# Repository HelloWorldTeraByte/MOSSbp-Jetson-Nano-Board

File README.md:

# MOSSbp-Jetson-Nano-Board
MOSSbp(Multi-material Open Source Secure Bio Printer) is an IoT connected bio printer. This is a daughter board for the jetson nano.

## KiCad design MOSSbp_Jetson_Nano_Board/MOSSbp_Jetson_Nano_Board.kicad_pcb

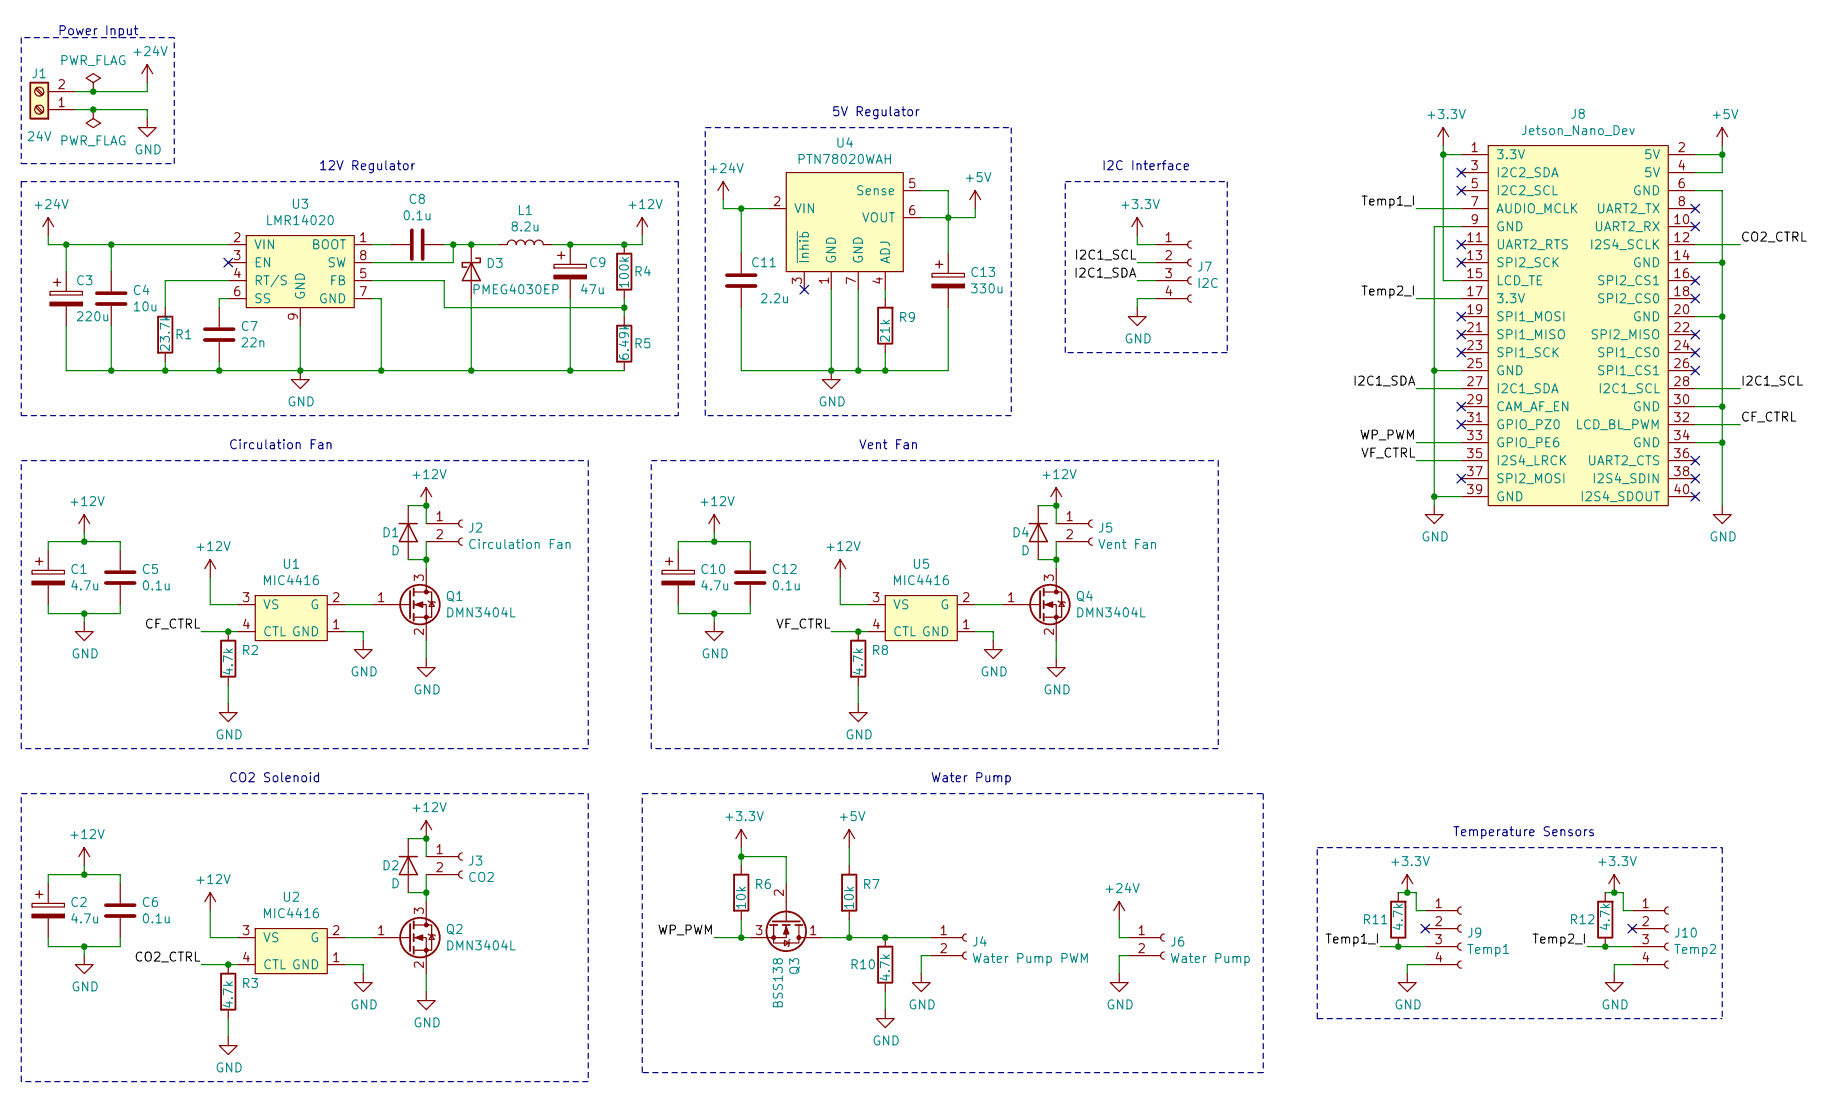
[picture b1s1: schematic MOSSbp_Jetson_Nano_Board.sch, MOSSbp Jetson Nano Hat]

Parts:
C1, C2, C10: 4.7u; C_1206_3216Metric_Pad1.42x1.75mm_HandSolder; Digi-Key_PN 478-11461-1-ND
C3: 220u; CP_Elec_8x10.5; Digi-Key_PN PCE5025CT-ND
C4: 10u; C_1206_3216Metric_Pad1.42x1.75mm_HandSolder; Digi-Key_PN 1276-6767-1-ND
C5, C6, C12: 0.1u; C_0603_1608Metric_Pad1.05x0.95mm_HandSolder; Digi-Key_PN 399-7845-1-ND
C7: 22n; C_0603_1608Metric_Pad1.05x0.95mm_HandSolder; Digi-Key_PN 399-3476-1-ND
C8: 0.1u; C_0603_1608Metric_Pad1.05x0.95mm_HandSolder; Digi-Key_PN 311-1341-1-ND
C9: 47u; C_2220_5650Metric_Pad1.97x5.40mm_HandSolder; Digi-Key_PN 445-7935-1-ND
C11: 2.2u; C_0603_1608Metric_Pad1.05x0.95mm_HandSolder; Digi-Key_PN 490-10486-1-ND
C13: 330u; CP_Elec_8x10; Digi-Key_PN PCE3888CT-ND
D1, D2, D4: D; D_SOD-123; Digi-Key_PN MBR130T1GOSDKR-ND
D3: PMEG4030EP; D_SOD-128; Digi-Key_PN 1727-5841-1-ND
J1: 24V; TerminalBlock_Phoenix_MKDS-1,5-2_1x02_P5.00mm_Horizontal; Digi-Key_PN 277-1667-ND
J2: Circulation Fan; JST_GH_BM02B-GHS-TBT_1x02-1MP_P1.25mm_Vertical; Digi-Key_PN 455-1578-1-ND
J3: CO2; JST_GH_BM02B-GHS-TBT_1x02-1MP_P1.25mm_Vertical; Digi-Key_PN 455-1578-1-ND
J4: Water Pump PWM; JST_GH_BM02B-GHS-TBT_1x02-1MP_P1.25mm_Vertical; Digi-Key_PN 455-1578-1-ND
J5: Vent Fan; JST_GH_BM02B-GHS-TBT_1x02-1MP_P1.25mm_Vertical; Digi-Key_PN 455-1578-1-ND
J6: Water Pump; JST_XH_B2B-XH-AM_1x02_P2.50mm_Vertical; Digi-Key_PN 455-2247-ND
J7: I2C; JST_GH_BM04B-GHS-TBT_1x04-1MP_P1.25mm_Vertical; Digi-Key_PN 455-1580-1-ND
J8: Jetson_Nano_Dev; PinHeader_2x20_P2.54mm_Vertical
J9: Temp1; JST_GH_BM04B-GHS-TBT_1x04-1MP_P1.25mm_Vertical; Digi-Key_PN 455-1580-1-ND
J10: Temp2; JST_GH_BM04B-GHS-TBT_1x04-1MP_P1.25mm_Vertical; Digi-Key_PN 455-1580-1-ND
L1: 8.2u; SRN8040-8R2Y; Digi-Key_PN SRN8040-8R2YCT-ND
Q1, Q2, Q4: DMN3404L; SOT-23; Digi-Key_PN DMN3404LDICT-ND
Q3: BSS138; SOT-23; Digi-Key_PN BSS138CT-ND
R1: 23.7k; R_0603_1608Metric_Pad1.05x0.95mm_HandSolder; Digi-Key_PN P23.7KHCT-ND
R2, R3, R8, R10, R11, R12: 4.7k; R_0603_1608Metric_Pad1.05x0.95mm_HandSolder; Digi-Key_PN 311-4.7KGRCT-ND
R4: 100k; R_0603_1608Metric_Pad1.05x0.95mm_HandSolder; Digi-Key_PN P100KDBCT-ND
R5: 6.49k; R_0603_1608Metric_Pad1.05x0.95mm_HandSolder; Digi-Key_PN P20065CT-ND
R6, R7: 10k; R_0603_1608Metric_Pad1.05x0.95mm_HandSolder; Digi-Key_PN 311-10.0KHRCT-ND
R9: 21k; R_0603_1608Metric_Pad1.05x0.95mm_HandSolder; Digi-Key_PN P21.0KHCT-ND
U1, U2, U5: MIC4416; SOT-143; Digi-Key_PN 576-1187-1-ND
U3: LMR14020; SOIC-8-1EP_3.9x4.9mm_P1.27mm_EP2.41x3.3mm; Digi-Key_PN 296-44320-1-ND
U4: PTN78020WAH; Digi-Key_PN 296-20515-ND

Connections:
+3V3: J7.1, J8.1 (3.3V), J8.15 (LCD_TE), J9.1, J10.1, Q3.2 (G), R6.1, R11.2, R12.2
+5V: C13.1, J8.2 (5V), J8.4 (5V), R7.1, U4.5 (Sense), U4.6 (VOUT)
+12V: C1.1, C2.1, C5.1, C6.1, C9.1, C10.1, C12.1, D1.1 (K), D2.1 (K), D4.1 (K), J2.1, J3.1, J5.1, L1.2, R4.1, U1.3 (VS), U2.3 (VS), U5.3 (VS)
+24V: C3.1, C4.1, C11.1, J1.2, J6.1, U3.2 (VIN), U4.2 (VIN)
/CF_CTRL: J8.32 (LCD_BL_PWM), R2.1, U1.4 (CTL)
/CO2_CTRL: J8.12 (I2S4_SCLK), R3.1, U2.4 (CTL)
/I2C1_SCL: J7.2, J8.28 (I2C1_SCL)
/I2C1_SDA: J7.3, J8.27 (I2C1_SDA)
/Temp1_I: J8.7 (AUDIO_MCLK), J9.3, R11.1
/Temp2_I: J8.17 (3.3V), J10.3, R12.1
/VF_CTRL: J8.35 (I2S4_LRCK), R8.1, U5.4 (CTL)
/WP_PWM: J8.33 (GPIO_PE6), Q3.3 (S), R6.2
GND: C1.2, C2.2, C3.2, C4.2, C5.2, C6.2, C7.2, C9.2, C10.2, C11.2, C12.2, C13.2, D3.2 (A), J1.1, J4.2, J6.2, J7.4, J8.6 (GND), J8.9 (GND), J8.14 (GND), J8.20 (GND), J8.25 (GND), J8.30 (GND), J8.34 (GND), J8.39 (GND), J9.4, J10.4, Q1.2 (S), Q2.2 (S), Q4.2 (S), R1.2, R2.2, R3.2, R5.2, R8.2, R9.1, R10.2, U1.1 (GND), U2.1 (GND), U3.7 (GND), U3.9 (GND), U4.1 (GND), U4.7 (GND), U5.1 (GND)
unnamed: C7.1, U3.6 (SS)
unnamed: C8.1, D3.1 (K), L1.1, U3.8 (SW)
unnamed: C8.2, U3.1 (BOOT)
unnamed: D1.2 (A), J2.2, Q1.3 (D)
unnamed: D2.2 (A), J3.2, Q2.3 (D)
unnamed: D4.2 (A), J5.2, Q4.3 (D)
unnamed: J4.1, Q3.1 (D), R7.2, R10.1
unnamed: Q1.1 (G), U1.2 (G)
unnamed: Q2.1 (G), U2.2 (G)
unnamed: Q4.1 (G), U5.2 (G)
unnamed: R1.1, U3.4 (RT/S)
unnamed: R4.2, R5.1, U3.5 (FB)
unnamed: R9.2, U4.4 (ADJ)

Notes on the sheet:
12V Regulator
Power Input
Circulation Fan
Vent Fan
CO2 Solenoid
Water Pump
5V Regulator
I2C Interface
Temperature Sensors

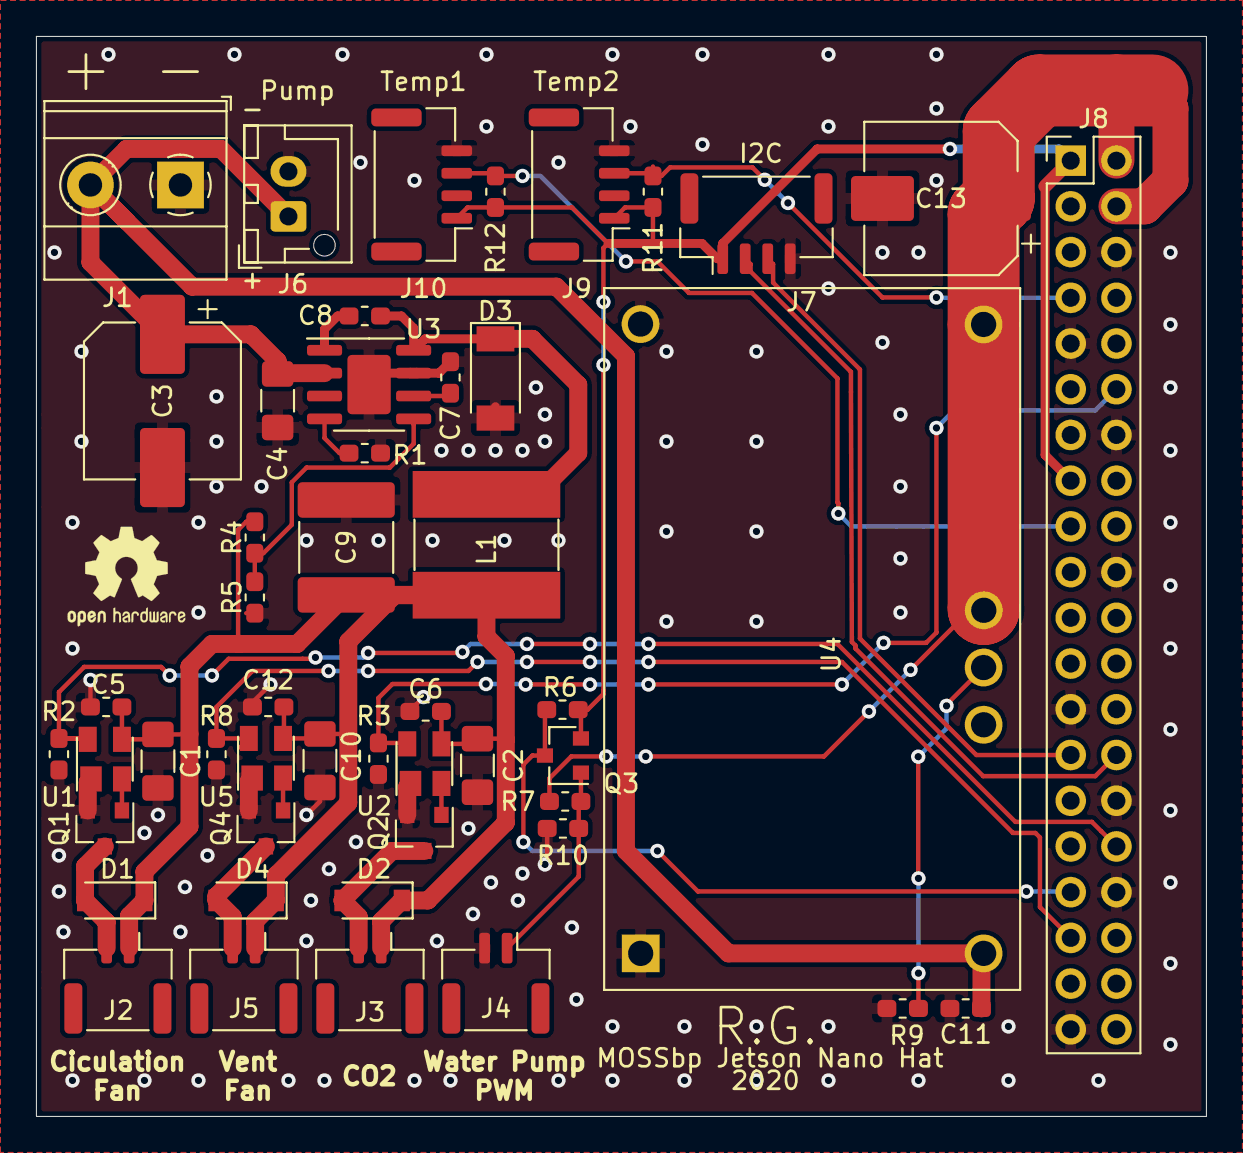
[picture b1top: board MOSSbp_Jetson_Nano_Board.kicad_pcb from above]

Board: 2 copper layers, 65.0 x 60.0 mm, 49 parts (0 on the bottom side), 26 nets.

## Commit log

2019-12-29 Added opensource CERN licence
2019-12-29 Added system architecture of the whole system
2019-12-31 Inital commit of PCB design
2020-01-15 Added 5V Regulator
2020-01-21 Changed the symbol library name
2020-01-23 Added fans and pump controls
2020-01-23 Added 5V regulator and control pins
2020-01-24 Added I2C interface and assigned parts
2020-01-24 Added footprint associations
2020-01-26 Finished assigning footprints and part numbers
2020-01-26 Started PCB design
2020-01-27 Finished PCB routing
2020-01-27 Adding temperature sensors
2020-01-27 Finished adding temp sensors
